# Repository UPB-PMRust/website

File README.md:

# MA Website

This is the website for the MA course delivered to ACS CC and FILS English.
\# DIY Smartwatch — Raspberry Pi Pico 2W + Rust

Proiect realizat de Alex22-ai.

Documentatie completa in smartwatch\_documentation.docx

Schema KiCad in smartwatch\_schema.kicad\_sch

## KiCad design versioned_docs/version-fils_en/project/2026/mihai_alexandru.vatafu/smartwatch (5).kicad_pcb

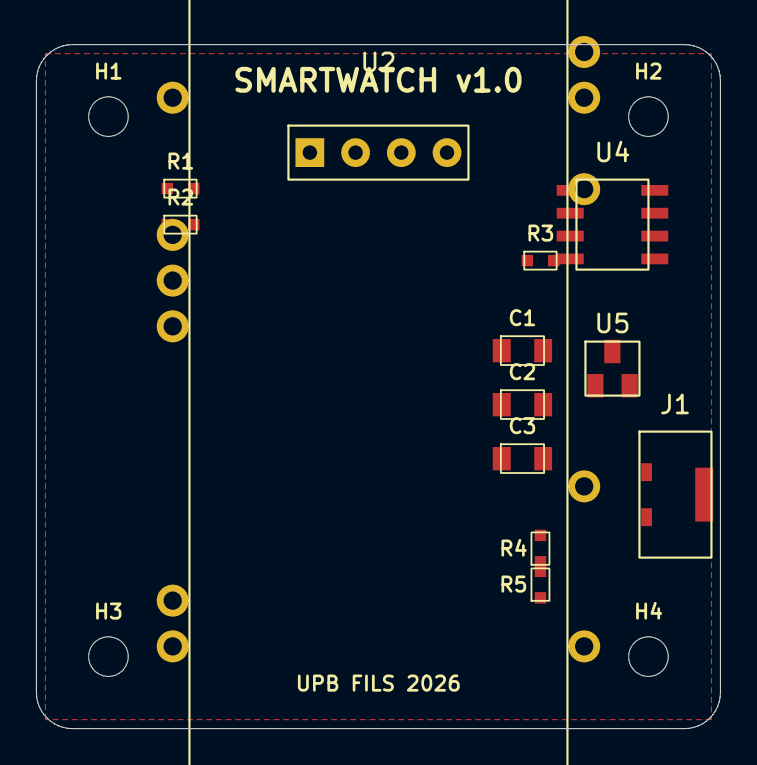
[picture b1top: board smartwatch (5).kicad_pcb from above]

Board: 2 copper layers, 38.0 x 38.0 mm, 18 parts (1 on the bottom side), 8 nets, no tracks yet.

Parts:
C1, C3: 10uF; C_0805_2012Metric
C2: 100nF; C_0402_1005Metric
H1, H2, H3, H4: MountingHole_M2; MountingHole_2.2mm_M2
J1: USB_C; USB_C_Receptacle_HRO_TYPE-C-31-M-12
R1, R2: 4.7k; R_0402_1005Metric
R3: 10k; R_0402_1005Metric
R4, R5: 100k; R_0402_1005Metric
U1: Raspberry_Pi_Pico_W; RPi_Pico_W
U2: SSD1306_OLED; PinHeader_1x04_P2.54mm_Vertical
U3: MAX30102; SOT-23-6
U4: TP4056; SOP-8_3.9x4.9mm_P1.27mm
U5: MCP1700-3302; SOT-23

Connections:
+3V3: C2.1, C3.1, R1.1, R2.1, U1.36, U2.1, U3.1, U3.6, U5.3
+5V: J1.A4, U4.1, U4.8
+VBAT: C1.1, R4.1, U1.39, U4.3, U5.1
GND: C1.2, C2.2, C3.2, J1.A1, J1.S1, R3.2, R5.2, U1.3, U1.8, U1.38, U2.2, U3.2, U4.2, U5.2
MAX30102_INT: U1.20, U3.5
SCL: R2.2, U1.7, U2.3, U3.3
SDA: R1.2, U1.6, U2.4, U3.4
VBAT_ADC: R4.2, R5.1, U1.31

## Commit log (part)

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2026-05-27 updating progress
2026-05-27 resizing webp
2026-05-27 updated the logs and added the pictures of the project
2026-05-27 Final Hardware photo and Documentation changes
2026-05-27 a few slides fixes to improve the content (#1363)
2026-05-27 Final documentation (#1359)
    * Added documentation for the project
    * Final documentation
2026-05-27 Kicad+architecture+more update
2026-05-27 Project/horatiu.oprea (#1287)
    * first_comm
    * add deadline
    * Asign Repo
    * Project documentation starter
    * Documentatie
    * Final Documentation
2026-05-27 Update index.md Kicad Scheme
2026-05-27 Add files via upload
    Hardware photos
2026-05-27 index.md updated
2026-05-28 Update software
    Changed KiCad schematic a bit + added some more info about software
2026-05-28 fix: resize device_back.webp to comply with 1024x768 resolution limit
2026-05-28 DIY Smartwatch - Pico 2W + Rust
2026-05-28 Add README
2026-05-28 Project/daria.niculescu (#1355)
    * docs
    * am adaugat diagrama
    * fixed image
    * added demo and completed the logs
    * modified photos type
    * hopefully fixed all images
2026-05-28 Add hardware photo and KiCad schematic
2026-05-28 examen
2026-05-28 docs: add final hardware photos
2026-05-28 docs: add missing closing parenthesis
2026-05-28 docs: add embedded-hal crate to software
2026-05-28 Project/albaidany (#1362)
    * my project
    * project update
    * project updated
    * Project folder changed to lower case
    * made changes
    * applied changes
2026-05-28 branch fix
2026-05-28 name change
2026-05-28 deleted file
2026-05-28 Final commit
2026-05-28 Final commit - resize images
2026-05-28 Optimize schematic SVG
2026-05-28 Updated Project
2026-05-28 Resize finalproject.webp
2026-05-28 Resize the photo.
2026-05-28 Finalize project documentation, BOM, and webp images
2026-05-28 Add schematic SVG file
2026-05-28 Replace SVG with PNG schematic, add weekly log
2026-05-28 Final updates
2026-05-28 Use WebP schematic image to pass CI check
2026-05-28 commitproject
2026-05-28 remove Zone.Identifier files
2026-05-28 fix: optimizat dimensiunea fisierelor svg si webp sub limita de 380KB
2026-05-28 Completed logs and crates list
2026-05-28 updated a library link
2026-05-28 added a wrong schematic.svg that was actually empty
2026-05-28 hardware
2026-05-28 added video proof
2026-05-28 final commit bye bye
2026-05-28 Update WEBP file sizes to fit properl parameters
2026-05-28 cod vai de capul lui
2026-05-28 updates2
2026-05-28 Fix MDX link syntax on line 8
2026-05-28 adjusted the resolution
2026-05-29 Add WebP compressed prototype photo
2026-05-29 image fix
2026-05-29 Final Website Version
2026-05-29 Added webp hardware images and finalized documentation
2026-05-29 Slightly changed description
2026-05-29 Update project documentation with author and link
    Added author information and GitHub project link to the project documentation.
2026-05-29 Fixed required issues for full commit
2026-05-29 final changes
2026-05-29 solve links problems.
2026-05-30 Week Logs Updated
2026-05-30 updated Andrei-Tudor Tanase project page (#1395)
2026-05-30 Project/andrei.tanase1012 (#1389)
    * .
    * 1
    * Project description
    * Project description
    * Project Documentation
    * Project Documentation
2026-05-30 Project/claudia.cranganu (#1383)
    * Smart Security System project
    * Update website/versioned_docs/version-fils_en/project/2026/claudia.cranganu/index.md
    * Added schematic image
    * Update Smart Security System final documentation
    * Update
    * Optimize schematic SVG
2026-05-30 Updated Documentation (#1376)
    * recovered from a corrupted version
    * Added PCB section and some new paragraphs
    * Finalized v1 of the documentation
    * Fixed image sizes
    * changed PCB images and added some text
    * Update website/versioned_docs/version-fils_en/project/2026/gabriel.stanciu2102/index.md
2026-05-30 fix: remove space from image filename and update reference
2026-05-30 Rename Shell.webp to shell.webp
2026-05-31 Added images and update documentation
2026-05-31 Validation push
2026-05-31 Add files via upload (#1424)
2026-05-31 Project/radu.vasilescu0510 (#1397)
    * Added documentation for the project
    * Final documentation
    * Fixed space problem
2026-05-31 Project Orion - Toros Dorian-Gabriel (#1399)
    * Add files via upload
    * Add files via upload
    * Add files via upload
    * Add images for weeks 11 to 17 May
    * Delete website/versioned_docs/version-fils_en/project/2026/dorian_gabriel.toros/images/ma9.webp
    * Add files via upload
2026-05-31 one final log bc I apparently forgot to commit my changes
2026-05-31 Project/andrei.codita final version (#1403)
    * Added project page - Andrei Codita
    * Updated links in the documentation
    * Add files via upload
    * Updated documentation and added KiCAD Scheme
    Updated the project documentation for the Tricopter including added milestones and SVG Schematic of the drone.
    * Deleted andrei.codita/MAProject.svg
2026-05-31 one final log bc I apparently forgot to commit my changes 2
2026-05-31 Project/alesia ana.burlacu (#1428)
    * Project Page - Digital Cuckoo Clock
    * Project Page - Digital Cuckoo Clock updated
    * Project Page - Digital Cuckoo Clock updated image
    * Digital Cuckoo Clock Project - hopefully the last commit before the first deadline
    * really the last commit
    * Hardware Milestione Commit
2026-05-31 Project/iana.zagornean (#1407)
    * Add project page for iana.zagornean
    * Update project page
    * Finish project
    ---------
2026-05-31 Update: Alexandru-Florin Neagu project - KaraBox - (Previously SteadyFrame) - after catastrophic hardware failure for first project (#1409)
    * Added SteadyFrame project documentation
    * Changed total cost to new correct number
    * Added github link for later usage, forgot to link it at the beginning
    * Changed svg file name to lowercase
    * Update website/versioned_docs/version-fils_en/project/2026/alexandru_florin.neagu/index.md
    Changed intro formatting to properly allign
2026-05-31 Final Documentation Update (#1394)
    * Update index.md
    * Add files via upload
2026-05-31 Project/eliza maria.manole (#1386)
    * Project-RoboMop
    Project
    * project-RoboMop
    Project
    * Apply suggestion from @frihetselsker
    * Update index.md
2026-05-31 Project/teodora.bosie (#1384)
    * Finalizare pagina documentatie si adaugare schema
    * fix image path
    * Reparare format imagine
    * Schimbare nume imagine in lower case
    * Trig pipeline update
    * Updated the image format and added week 10
2026-05-31 Update weekly logs, crates and hardware photos for Project/andrei.mardale0703 (#1374)
    * docs: add diagram
    * docs: initial documentation page
    * fix: formatting
    * docs: update motivation
    * docs: add eeprom24x crate to software section
    * fix: formatting
2026-05-31 Docs Update: Week 14 Progress & Final Documentation (Emilian-Valentin Balasa) (#1371)
    * Added initial project documentation
    * Added architecture.png and finalized documentation
    * Updated documentation format to match official template
    * Updated diagram to SVG format to comply with project requirements
    * Final version of documentation following official template
    * Final polish for Milestone 1 documentation
2026-05-31 Project/alexandros.tzikas (#1368)
    * Add project page for alexandros.tzikas
    * Alexandros Tzikas project documentation
    * weekly log update
    * Update log/add schematics
    * fixed schematics+hardware+log update
    * Update to log + other things
2026-05-31 Project/yelyzaveta.lysenko (#1367)
    * Add project page for yelyzaveta.lysenko
    * Update SchoolGate README / docs
    * Add GitHub project link
    * Add schematic
    * Remove Zone.Identifier file
    * Update schematic
2026-05-31 Project/mihai.porojan (#1365)
    * santosaniaitoiai
    * Changed .svg file to lowercase
    * Fix image filename case for architecture diagram
    * hardware milestone
    * .
    * week 10
2026-05-31 Final pull req : Lie Detector
2026-05-31 Week 14 Documentation Update (#1406)
    * Add project description for RustShips
    * docs: add inspiration and resource links
    * added: image paths in index.md
    * updated: architecture scheme in index.md
    * docs: optimize 3D PCB render images to webp format
    * fix: resize and compress images to pass repo size limits
2026-05-31 Add full hardware schematic image
2026-05-31 Project/iris alexandra.vavilov (#1415)
    * init
    * Iris Vavilov images fixed
    * Iris Vavilov removed problematic image
    * final iris_alexandra.vavilov
    * Update project documentation with author and link
    Added author information and GitHub project link to the project documentation.
2026-05-31 Resize image
2026-05-31 Rename image to lowercase
2026-05-31 Final documentation
2026-05-31 image resolution modification
2026-06-01 Final changes 1.0
2026-06-01 Final doc fix
2026-06-01 KaraBox Final Documentation (#1435)
    * Added SteadyFrame project documentation
    * Changed total cost to new correct number
    * Added github link for later usage, forgot to link it at the beginning
    * Changed svg file name to lowercase
    * Update website/versioned_docs/version-fils_en/project/2026/alexandru_florin.neagu/index.md
    Changed intro formatting to properly allign
2026-06-01 Fixed image duplication
2026-06-01 Correct Sizes
2026-06-01 Fixed final update (#1436)
    * updated project page - Rock, Paper, Scissors
    * Update website/versioned_docs/version-fils_en/project/2026/emilia.petre/index.md
    * Swapped SVG file
    * Project
    * Fixed final update
    * Fixed image
2026-06-01 Final documentation (#1433)
2026-06-02 Add PicoReflex project page with schematic (#1129)
    * Add PicoReflex project page with schematic
    * Add schematic SVG file
    * Replace SVG with PNG schematic, add weekly log
    * Use WebP schematic image to pass CI check
    * Resize schematic WebP to fit resolution limit
2026-06-02 Project/cristian.gociu0401 (#1425)
    * Update documentation
    * First version
    * Add Architecture diagram
    * Update index architecture schematic.md
    * Update index.md
    * Update indexV2.md
2026-06-02 fixed schematic
2026-06-02 final pull request
2026-06-03 Revert "update"
    This reverts commit cddccbef32878bfd876e4de8947fdf90535a07af.
2026-06-03 Added photos of the project
2026-06-05 Project/mihai.temiac Final Push, new photos (#1439)
    * added documentation
    * hardware and schematics
    * final pull request
    ---------
2026-06-06 Second update (#1404)
    * Fisier index si imagine salvate
    * update imagine
    * update
    * update2
    * Remove unwanted image files
    * update
2026-06-09 fix: remove duplicate explanation ( already in the table above)
2026-06-09 fix: update MPU-6000 to MPU-6500 and fix anchor links in Lab 05
2026-06-12 first commit (#936)
    * first commit
    * second commit
    * Added Hardware Photo and Electrical KICad Scheme
    * fix: optimizat dimensiunea fisierelor svg si webp sub limita de 380KB
    * Correct Sizes
    ---------
